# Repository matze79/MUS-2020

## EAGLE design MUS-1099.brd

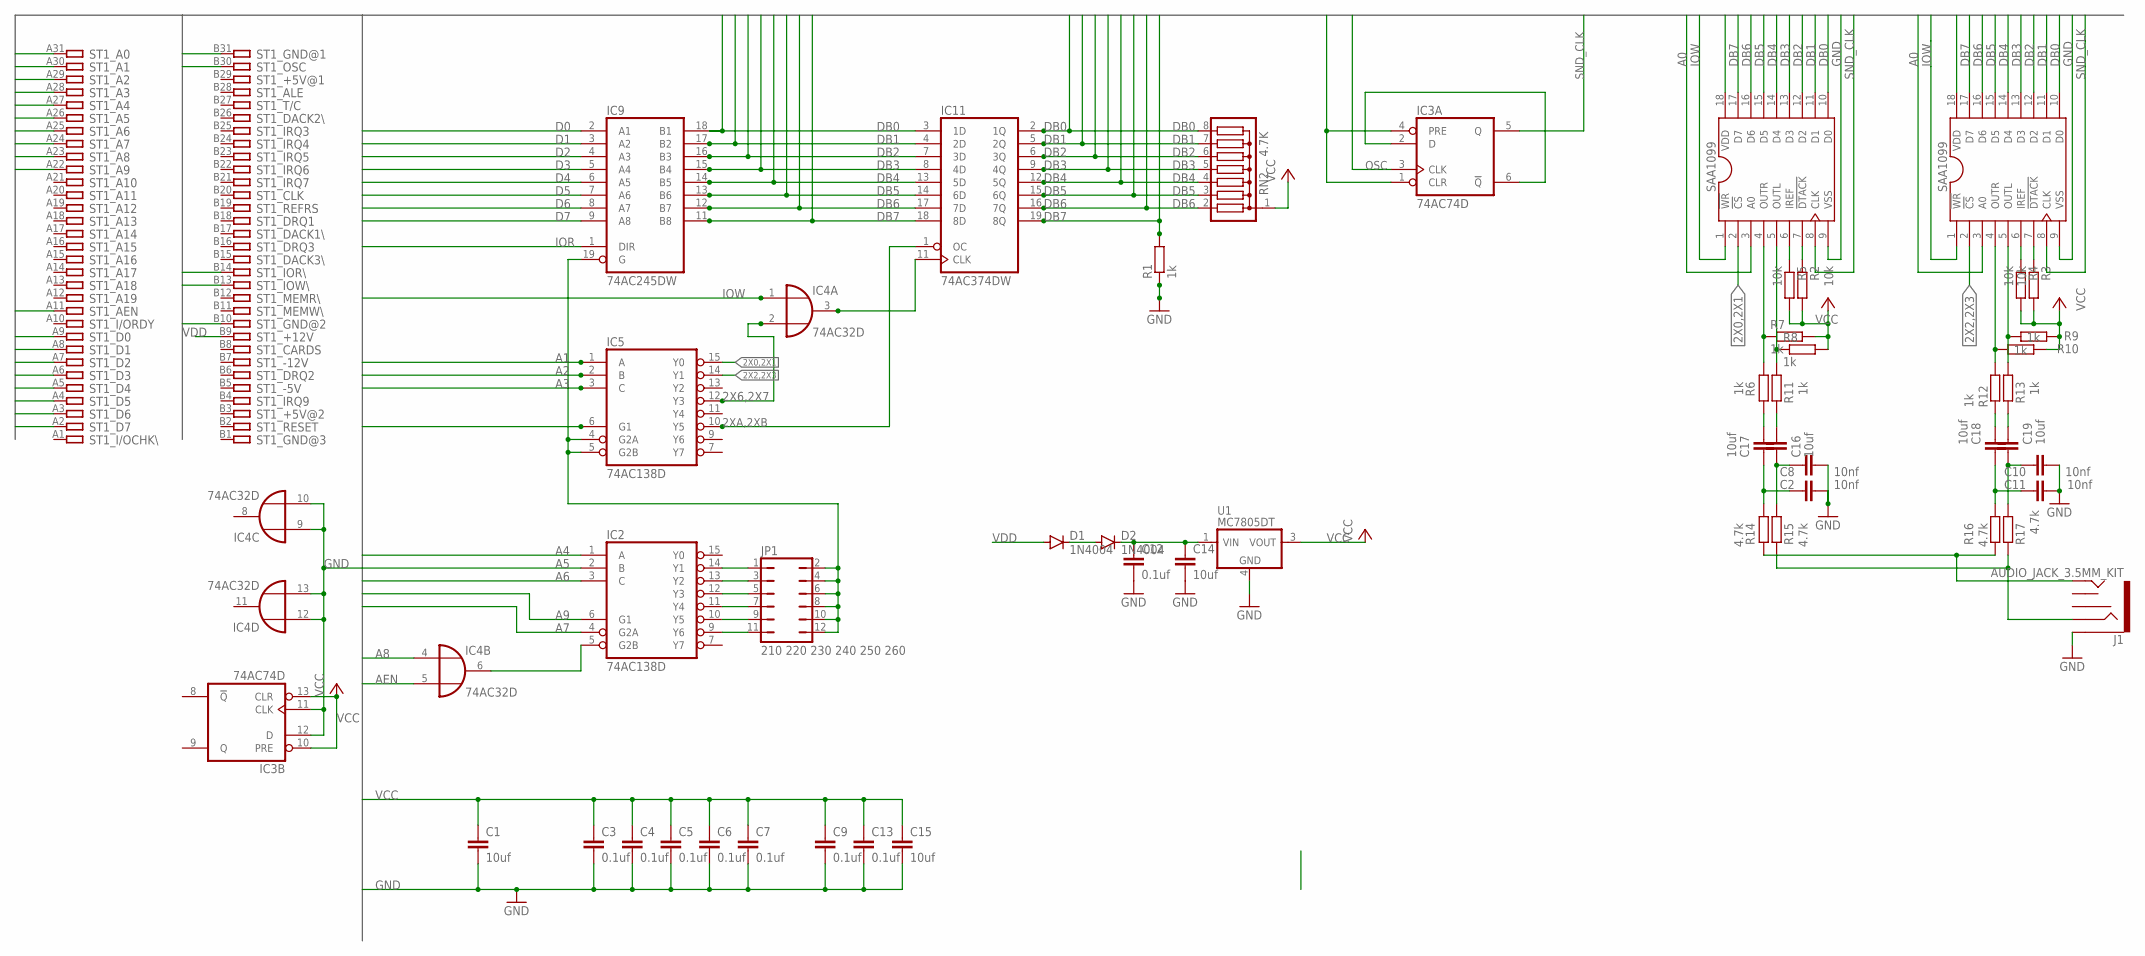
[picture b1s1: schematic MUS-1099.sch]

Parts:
C1: 10uf; C0805
C2, C8, C10, C11: 10nf; C0805K
C3, C4, C5, C6, C7, C9, C12, C13: 0.1uf; C0805
C14, C15, C16, C17, C18, C19: 10uf; C0805K
D1, D2: 1N4004; DO41-10
IC2, IC5: 74AC138D; SO16
IC3: 74AC74D; SO14
IC4: 74AC32D; SO14
IC7, IC8: SAA1099; DIL18
IC9: 74AC245DW; SO20W
IC11: 74AC374DW; SO20W
J1: AUDIO_JACK_3.5MM_KIT; AUDIO-JACK-KIT
JP1: 210 220 230 240 250 260; JP6Q
R1, R6, R7, R8, R9, R10, R11, R12, R13: 1k; R0805
R2, R3, R4, R5: 10k; R0805
R14, R15, R16, R17: 4.7k; R0805
RN2: 4.7K; SIL8
ST1: 8 bit ISA; IBM8BIT
U1: MC7805DT; DPAK-3

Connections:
2X0,2X1: IC5.15 (Y0), IC7.2 (!CS!)
2X2,2X3: IC5.14 (Y1), IC8.2 (!CS!)
2X6,2X7: IC4.2 (I1), IC5.12 (Y3)
2XA,2XB: IC5.10 (Y5), IC11.1 (OC)
A0: IC7.3 (A0), IC8.3 (A0), ST1.A31
A1: IC5.1 (A), ST1.A30
A2: IC5.2 (B), ST1.A29
A3: IC5.3 (C), ST1.A28
A4: IC2.1 (A), ST1.A27
A5: IC2.2 (B), ST1.A26
A6: IC2.3 (C), ST1.A25
A7: IC2.4 (G2A), ST1.A24
A8: IC4.4 (I0), ST1.A23
A9: IC2.6 (G1), ST1.A22
AEN: IC4.5 (I1), ST1.A11
D0: IC9.2 (A1), ST1.A9
D1: IC9.3 (A2), ST1.A8
D2: IC9.4 (A3), ST1.A7
D3: IC9.5 (A4), ST1.A6
D4: IC9.6 (A5), ST1.A5
D5: IC9.7 (A6), ST1.A4
D6: IC9.8 (A7), ST1.A3
D7: IC9.9 (A8), ST1.A2
DB0: IC7.10 (D0), IC8.10 (D0), IC9.18 (B1), IC11.2 (1Q), IC11.3 (1D), RN2.8
DB1: IC7.11 (D1), IC8.11 (D1), IC9.17 (B2), IC11.4 (2D), IC11.5 (2Q), RN2.7
DB2: IC7.12 (D2), IC8.12 (D2), IC9.16 (B3), IC11.6 (3Q), IC11.7 (3D), RN2.6
DB3: IC7.13 (D3), IC8.13 (D3), IC9.15 (B4), IC11.8 (4D), IC11.9 (4Q), RN2.5
DB4: IC7.14 (D4), IC8.14 (D4), IC9.14 (B5), IC11.12 (5Q), IC11.13 (5D), RN2.4
DB5: IC7.15 (D5), IC8.15 (D5), IC9.13 (B6), IC11.14 (6D), IC11.15 (6Q), RN2.3
DB6: IC7.16 (D6), IC8.16 (D6), IC9.12 (B7), IC11.16 (7Q), IC11.17 (7D), RN2.2
DB7: IC7.17 (D7), IC8.17 (D7), IC9.11 (B8), IC11.18 (8D), IC11.19 (8Q), R1.2
GND: C1.2, C2.2, C3.2, C4.2, C5.2, C6.2, C7.2, C8.2, C9.2, C10.2, C11.2, C12.2, C13.2, C14.2, C15.2, IC2.8 (GND), IC3.7 (GND), IC3.11 (CLK), IC3.12 (D), IC4.7 (GND), IC4.9 (I0), IC4.10 (I1), IC4.12 (I0), IC4.13 (I1), IC5.8 (GND), IC7.9 (VSS), IC8.9 (VSS), IC9.10 (GND), IC11.10 (GND), J1.SLEEVE, R1.1, ST1.B10, ST1.B31, U1.4 (GND)
IOR: IC9.1 (DIR), ST1.B14
IOW: IC4.1 (I0), IC7.1 (!WR!), IC8.1 (!WR!), ST1.B13
N210: IC2.14 (Y1), JP1.1
N220: IC2.13 (Y2), JP1.3
N230: IC2.12 (Y3), JP1.5
N240: IC2.11 (Y4), JP1.7
N250: IC2.10 (Y5), JP1.9
N260: IC2.9 (Y6), JP1.11
unnamed: IC2.5 (G2B), IC4.6 (O)
unnamed: IC7.6 (IREF), R5.1
unnamed: IC7.7 (!DTACK!), R2.1
unnamed: IC8.7 (!DTACK!), R3.1
unnamed: IC8.6 (IREF), R4.1
unnamed: IC7.4 (OUTR), R6.1, R7.1
unnamed: IC5.4 (G2A), IC5.5 (G2B), IC9.19 (G), JP1.2, JP1.4, JP1.6, JP1.8, JP1.10, JP1.12
unnamed: IC7.5 (OUTL), R8.1, R11.1
unnamed: IC4.3 (O), IC11.11 (CLK)
unnamed: IC3.2 (D), IC3.6 (!Q)
unnamed: IC8.4 (OUTR), R10.2, R12.2
unnamed: IC8.5 (OUTL), R9.2, R13.1
unnamed: C2.1, C17.2, R14.1
unnamed: C8.1, C16.2, R15.1
unnamed: C11.1, C18.2, R16.1
unnamed: C10.1, C19.2, R17.1
unnamed: J1.RING, R15.2, R17.2
unnamed: J1.TIP, R14.2, R16.2
unnamed: D1.C, D2.A
unnamed: C12.1, C14.1, D2.C, U1.1 (VIN)
unnamed: C17.1, R6.2
unnamed: C16.1, R11.2
unnamed: C18.1, R12.1
unnamed: C19.1, R13.2
OSC: IC3.3 (CLK), ST1.B30
SND_CLK: IC3.5 (Q), IC7.8 (CLK), IC8.8 (CLK)
VCC: C1.1, C3.1, C4.1, C5.1, C6.1, C7.1, C9.1, C13.1, C15.1, IC2.16 (VCC), IC3.1 (CLR), IC3.4 (PRE), IC3.10 (PRE), IC3.13 (CLR), IC3.14 (VCC), IC4.14 (VCC), IC5.6 (G1), IC5.16 (VCC), IC7.18 (VDD), IC8.18 (VDD), IC9.20 (VCC), IC11.20 (VCC), R2.2, R3.2, R4.2, R5.2, R7.2, R8.2, R9.1, R10.1, RN2.1, U1.3 (VOUT)
VDD: D1.A, ST1.B9

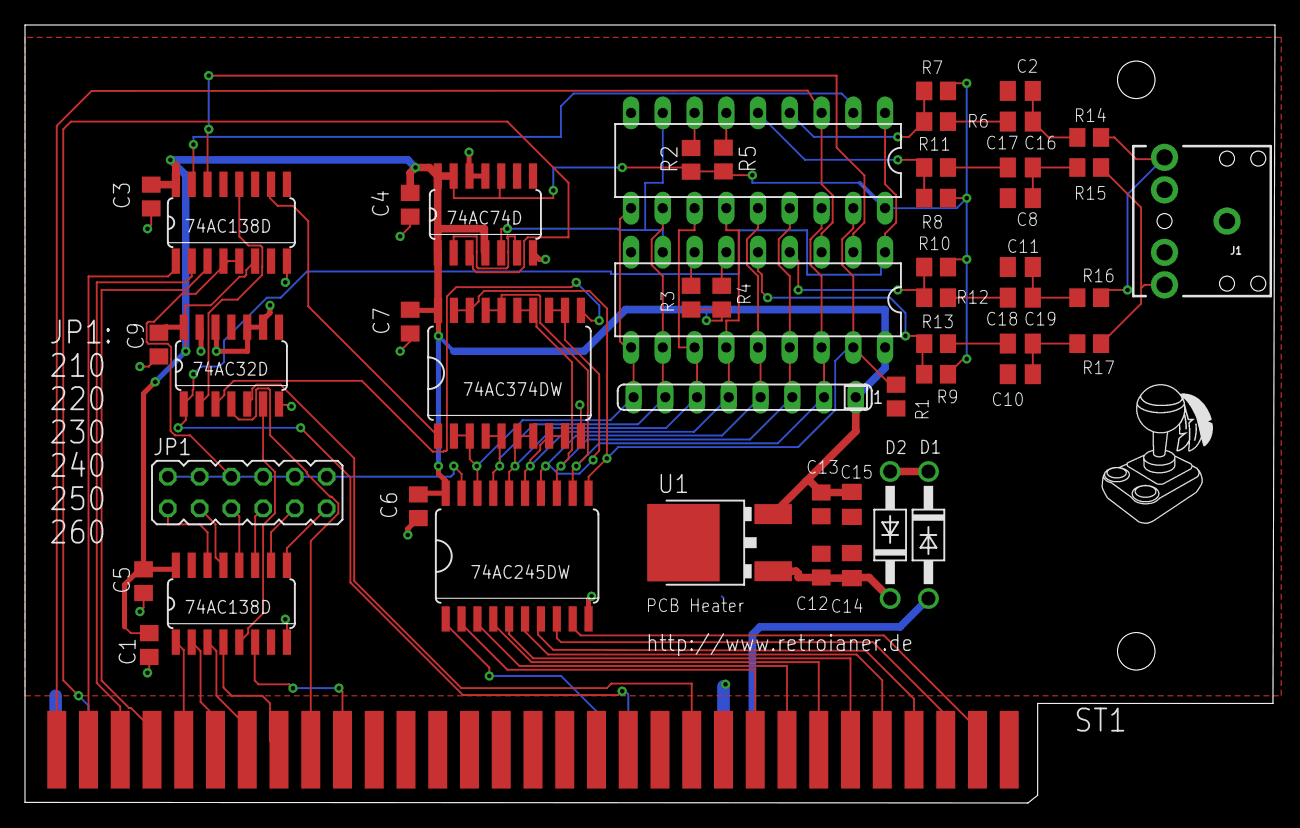
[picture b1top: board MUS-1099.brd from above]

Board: 2 copper layers, 100.0 x 62.2 mm, 51 parts (0 on the bottom side), 68 nets.

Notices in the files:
parts and their libraries:
SparkFun-Connectors: Licensing: Creative Commons ShareAlike 4.0 International - https://creativecommons.org/licenses/by-sa/4.0
